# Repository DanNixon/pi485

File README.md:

# pi485

Simple module for interfacing RS485 devices with an Ethernet network.

## Features

- Two RS485-UART interfaces
- Ethernet (either [WIZ550io](https://docs.wiznet.io/Product/ioModule/wiz550io) or [W5500-EVB-Pico](https://docs.wiznet.io/Product/iEthernet/W5500/w5500-evb-pico))
- SD card
- 5V regulator
- Display and buttons

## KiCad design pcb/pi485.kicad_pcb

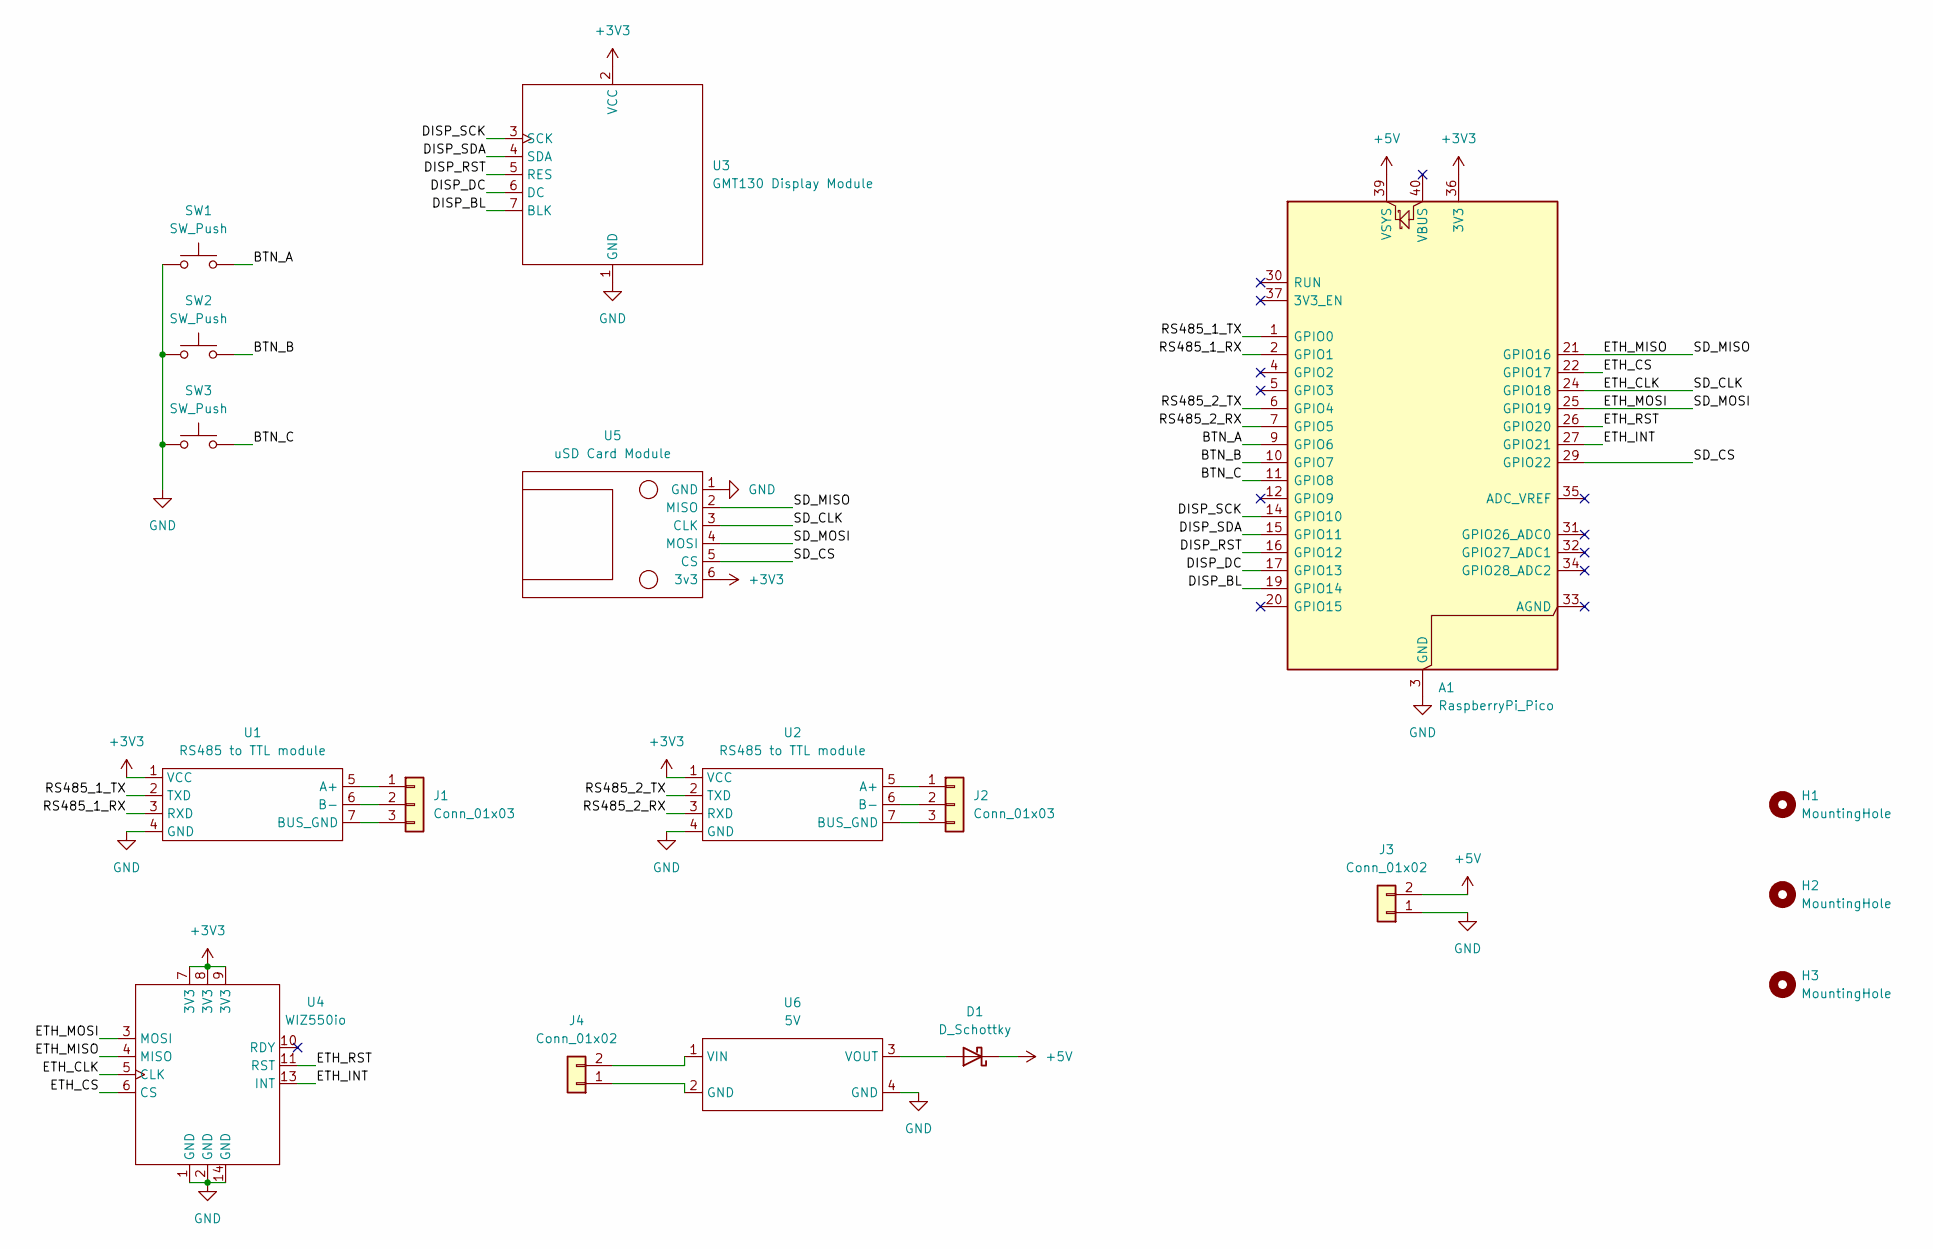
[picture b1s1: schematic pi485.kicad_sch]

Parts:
A1: RaspberryPi_Pico; RaspberryPi_Pico_Common_THT
D1: D_Schottky; D_SOD-123
H1, H2, H3: MountingHole; MountingHole_3.2mm_M3
J1, J2: Conn_01x03; CTB7000-3
J3, J4: Conn_01x02; ED5552DS
SW1, SW2, SW3: SW_Push; SW_PUSH_6mm
U1, U2: RS485 to TTL module; RS485_to_ttl
U3: GMT130 Display Module; GMT130
U4: WIZ550io
U5: uSD Card Module; uSD_Card
U6: 5V; AliE_MP1584EN_regulator

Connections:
+3V3: A1.36 (3V3), U1.1 (VCC), U2.1 (VCC), U3.2 (VCC), U4.7 (3V3), U4.8 (3V3), U4.9 (3V3), U5.6 (3v3)
+5V: A1.39 (VSYS), D1.1 (K), J3.2
/BTN_A: A1.9 (GPIO6), SW1.2
/BTN_B: A1.10 (GPIO7), SW2.2
/BTN_C: A1.11 (GPIO8), SW3.2
/DISP_BL: A1.19 (GPIO14), U3.7 (BLK)
/DISP_DC: A1.17 (GPIO13), U3.6 (DC)
/DISP_RST: A1.16 (GPIO12), U3.5 (RES)
/DISP_SCK: A1.14 (GPIO10), U3.3 (SCK)
/DISP_SDA: A1.15 (GPIO11), U3.4 (SDA)
/ETH_CLK: A1.24 (GPIO18), U4.5 (CLK), U5.3 (CLK)
/ETH_CS: A1.22 (GPIO17), U4.6 (CS)
/ETH_INT: A1.27 (GPIO21), U4.13 (INT)
/ETH_MISO: A1.21 (GPIO16), U4.4 (MISO), U5.2 (MISO)
/ETH_MOSI: A1.25 (GPIO19), U4.3 (MOSI), U5.4 (MOSI)
/ETH_RST: A1.26 (GPIO20), U4.11 (RST)
/RS485_1_RX: A1.2 (GPIO1), U1.3 (RXD)
/RS485_1_TX: A1.1 (GPIO0), U1.2 (TXD)
/RS485_2_RX: A1.7 (GPIO5), U2.3 (RXD)
/RS485_2_TX: A1.6 (GPIO4), U2.2 (TXD)
/SD_CS: A1.29 (GPIO22), U5.5 (CS)
GND: A1.3 (GND), A1.8 (GND), A1.13 (GND), A1.18 (GND), A1.23 (GND), A1.28 (GND), A1.38 (GND), J3.1, SW1.1, SW2.1, SW3.1, U1.4 (GND), U2.4 (GND), U3.1 (GND), U4.1 (GND), U4.2 (GND), U4.14 (GND), U5.1 (GND), U6.4 (GND)
unnamed: D1.2 (A), U6.3 (VOUT)
unnamed: J1.1, U1.5 (A+)
unnamed: J1.2, U1.6 (B-)
unnamed: J1.3, U1.7 (BUS_GND)
unnamed: J2.1, U2.5 (A+)
unnamed: J2.2, U2.6 (B-)
unnamed: J2.3, U2.7 (BUS_GND)
unnamed: J4.1, U6.2 (GND)
unnamed: J4.2, U6.1 (VIN)

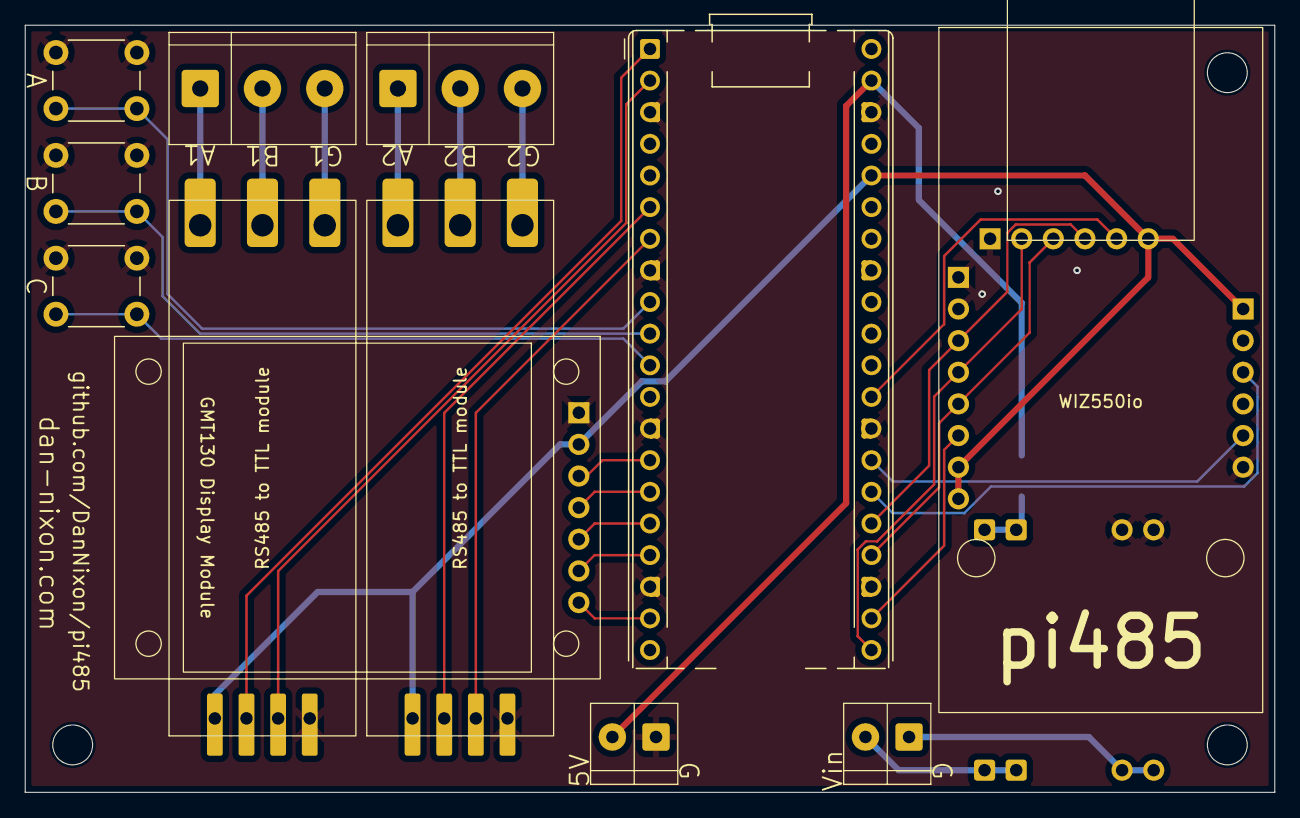
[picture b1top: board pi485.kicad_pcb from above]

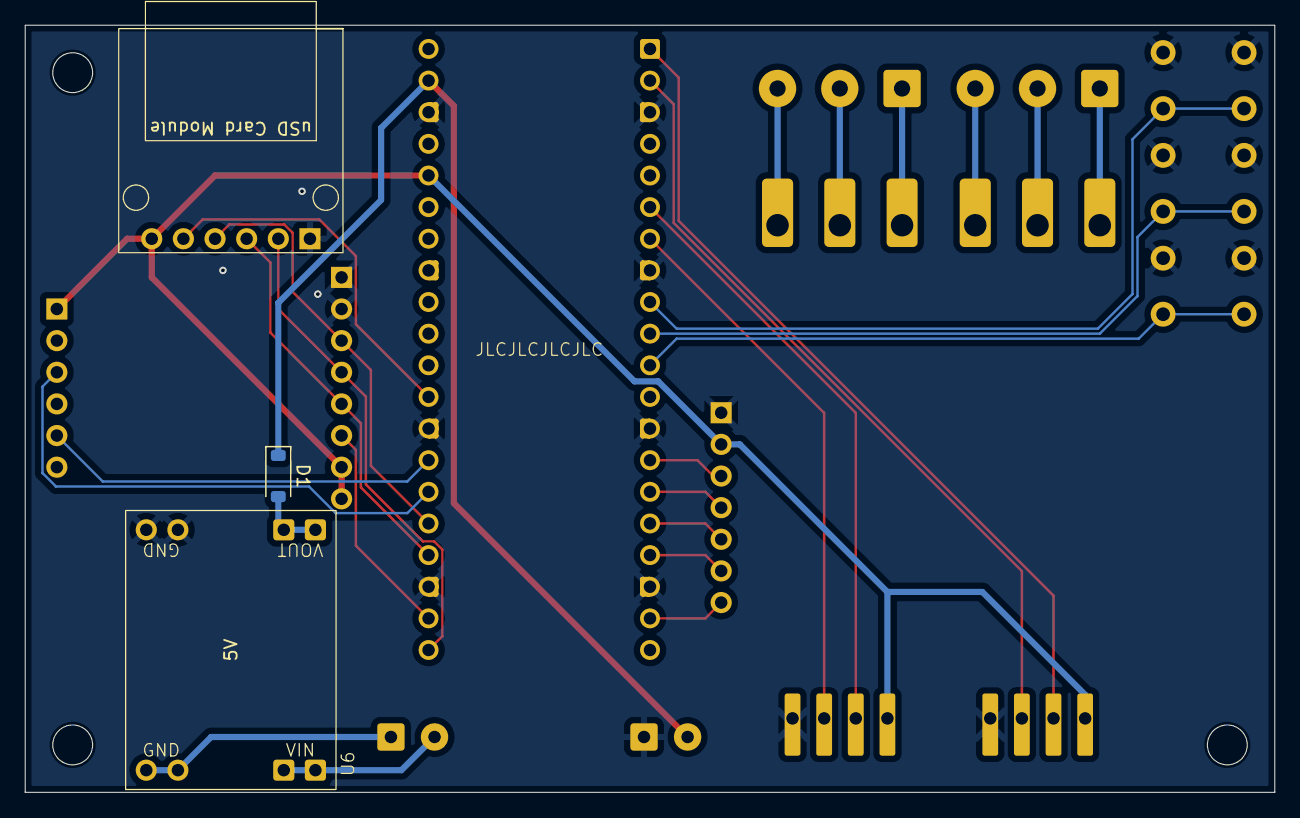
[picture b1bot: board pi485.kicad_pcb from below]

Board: 2 copper layers, 100.3 x 61.6 mm, 18 parts (3 on the bottom side), 31 nets.

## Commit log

2025-08-24 Bump actions/checkout from 4 to 5
    Bumps [actions/checkout](https://github.com/actions/checkout) from 4 to 5.
    - [Release notes](https://github.com/actions/checkout/releases)
    - [Changelog](https://github.com/actions/checkout/blob/main/CHANGELOG.md)
    - [Commits](https://github.com/actions/checkout/compare/v4...v5)
    ---
    updated-dependencies:
2025-08-25 Move demo firmware to subdirectory
2025-08-25 USB-RS485 adapter firmware
2025-08-27 Log data in RS485 USB adapter
